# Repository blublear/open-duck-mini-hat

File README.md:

# Pi Hat for the [Open Duck Mini](https://github.com/apirrone/Open_Duck_Mini)

The connectors are XH 2.54mm

Make sure the pin numbers in the schematic matches your setup.

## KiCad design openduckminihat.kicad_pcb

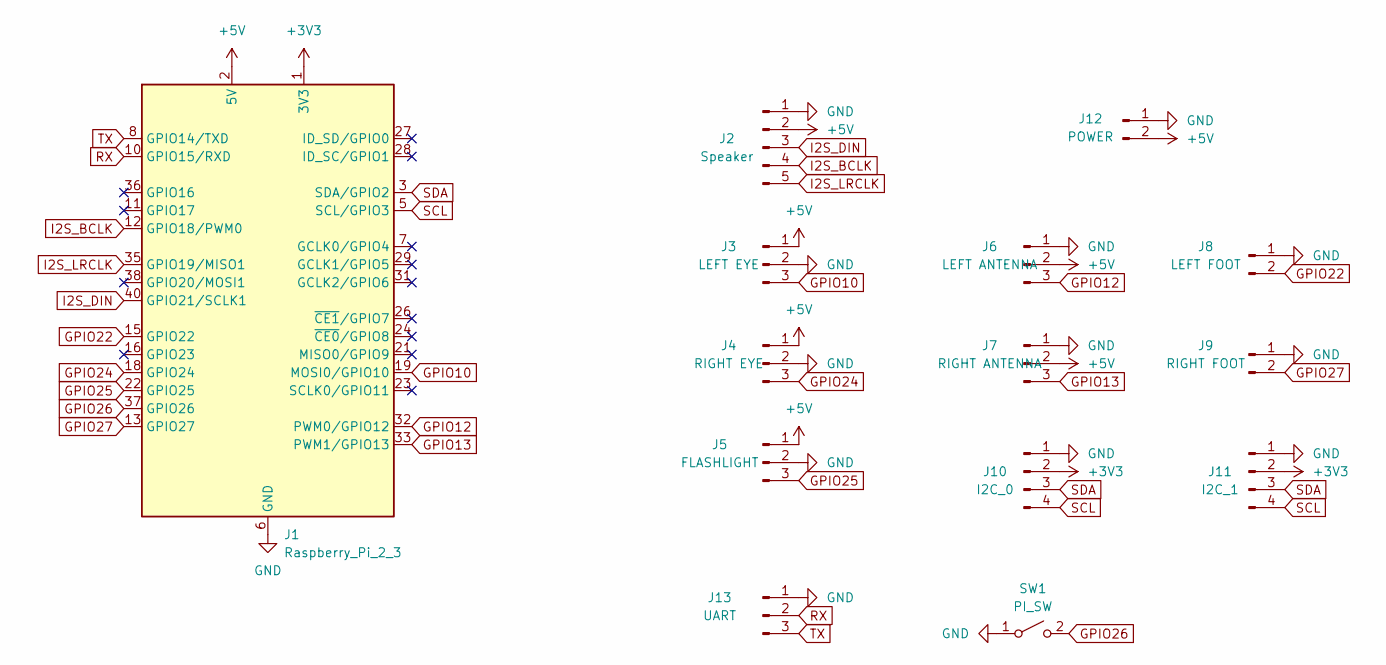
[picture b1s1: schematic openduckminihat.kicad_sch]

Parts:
J1: Raspberry_Pi_2_3; PinSocket_2x20_P2.54mm_Vertical
J2: Speaker; JST_XH_B5B-XH-A_1x05_P2.50mm_Vertical
J3: LEFT EYE; JST_XH_B3B-XH-A_1x03_P2.50mm_Vertical
J4: RIGHT EYE; JST_XH_B3B-XH-A_1x03_P2.50mm_Vertical
J5: FLASHLIGHT; JST_XH_B3B-XH-A_1x03_P2.50mm_Vertical
J6: LEFT ANTENNA; JST_XH_B3B-XH-A_1x03_P2.50mm_Vertical
J7: RIGHT ANTENNA; JST_XH_B3B-XH-A_1x03_P2.50mm_Vertical
J8: LEFT FOOT; JST_XH_B2B-XH-A_1x02_P2.50mm_Vertical
J9: RIGHT FOOT; JST_XH_B2B-XH-A_1x02_P2.50mm_Vertical
J10: I2C_0; JST_XH_B4B-XH-A_1x04_P2.50mm_Vertical
J11: I2C_1; JST_XH_B4B-XH-A_1x04_P2.50mm_Vertical
J12: POWER; JST_XH_B2B-XH-A_1x02_P2.50mm_Vertical
J13: UART; JST_XH_B3B-XH-A_1x03_P2.50mm_Vertical
SW1: PI_SW; JST_XH_B2B-XH-A_1x02_P2.50mm_Vertical

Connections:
+3V3: J1.1 (3V3), J1.17 (3V3), J10.2, J11.2
+5V: J1.2 (5V), J1.4 (5V), J2.2, J3.1, J4.1, J5.1, J6.2, J7.2, J12.2
GND: J1.6 (GND), J1.9 (GND), J1.14 (GND), J1.20 (GND), J1.25 (GND), J1.30 (GND), J1.34 (GND), J1.39 (GND), J2.1, J3.2, J4.2, J5.2, J6.1, J7.1, J8.1, J9.1, J10.1, J11.1, J12.1, J13.1, SW1.1 (A)
GPIO10: J1.19 (MOSI0/GPIO10), J3.3
GPIO12: J1.32 (PWM0/GPIO12), J6.3
GPIO13: J1.33 (PWM1/GPIO13), J7.3
GPIO22: J1.15 (GPIO22), J8.2
GPIO24: J1.18 (GPIO24), J4.3
GPIO25: J1.22 (GPIO25), J5.3
GPIO26: J1.37 (GPIO26), SW1.2 (B)
GPIO27: J1.13 (GPIO27), J9.2
I2S_BCLK: J1.12 (GPIO18/PWM0), J2.4
I2S_DIN: J1.40 (GPIO21/SCLK1), J2.3
I2S_LRCLK: J1.35 (GPIO19/MISO1), J2.5
RX: J1.10 (GPIO15/RXD), J13.2
SCL: J1.5 (SCL/GPIO3), J10.4, J11.4
SDA: J1.3 (SDA/GPIO2), J10.3, J11.3
TX: J1.8 (GPIO14/TXD), J13.3

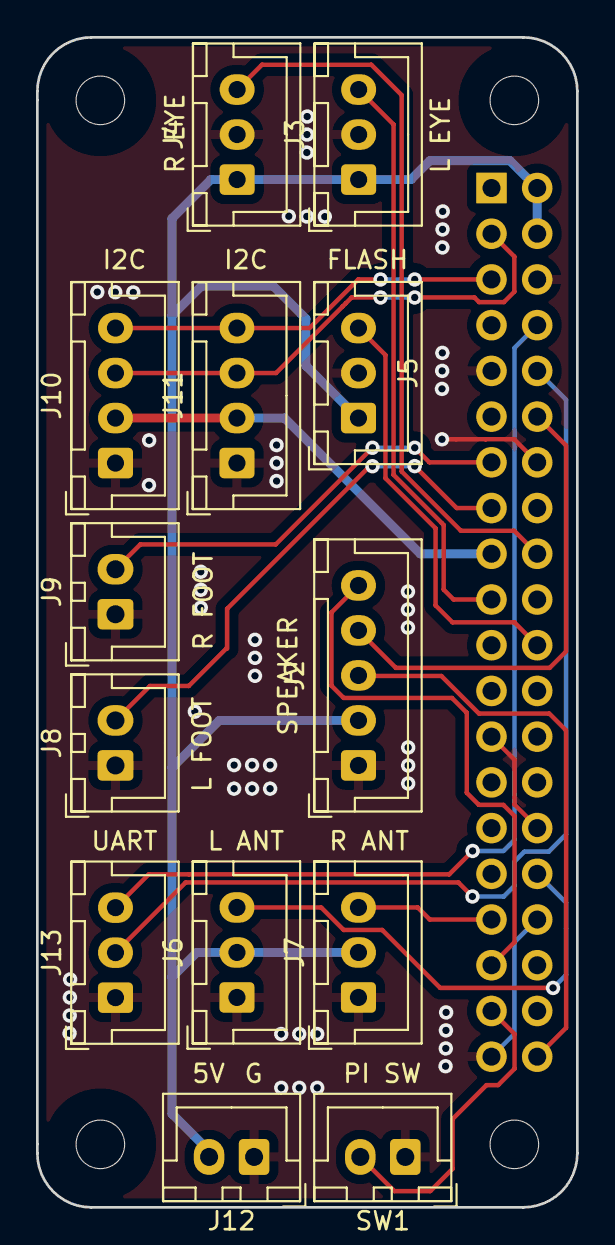
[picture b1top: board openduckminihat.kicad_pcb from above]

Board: 2 copper layers, 30.0 x 65.0 mm, 18 parts (1 on the bottom side), 18 nets.

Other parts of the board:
H1, H2, H3, H4: MountingHole; MountingHole_2.7mm_M2.5_uHAT_RPi
